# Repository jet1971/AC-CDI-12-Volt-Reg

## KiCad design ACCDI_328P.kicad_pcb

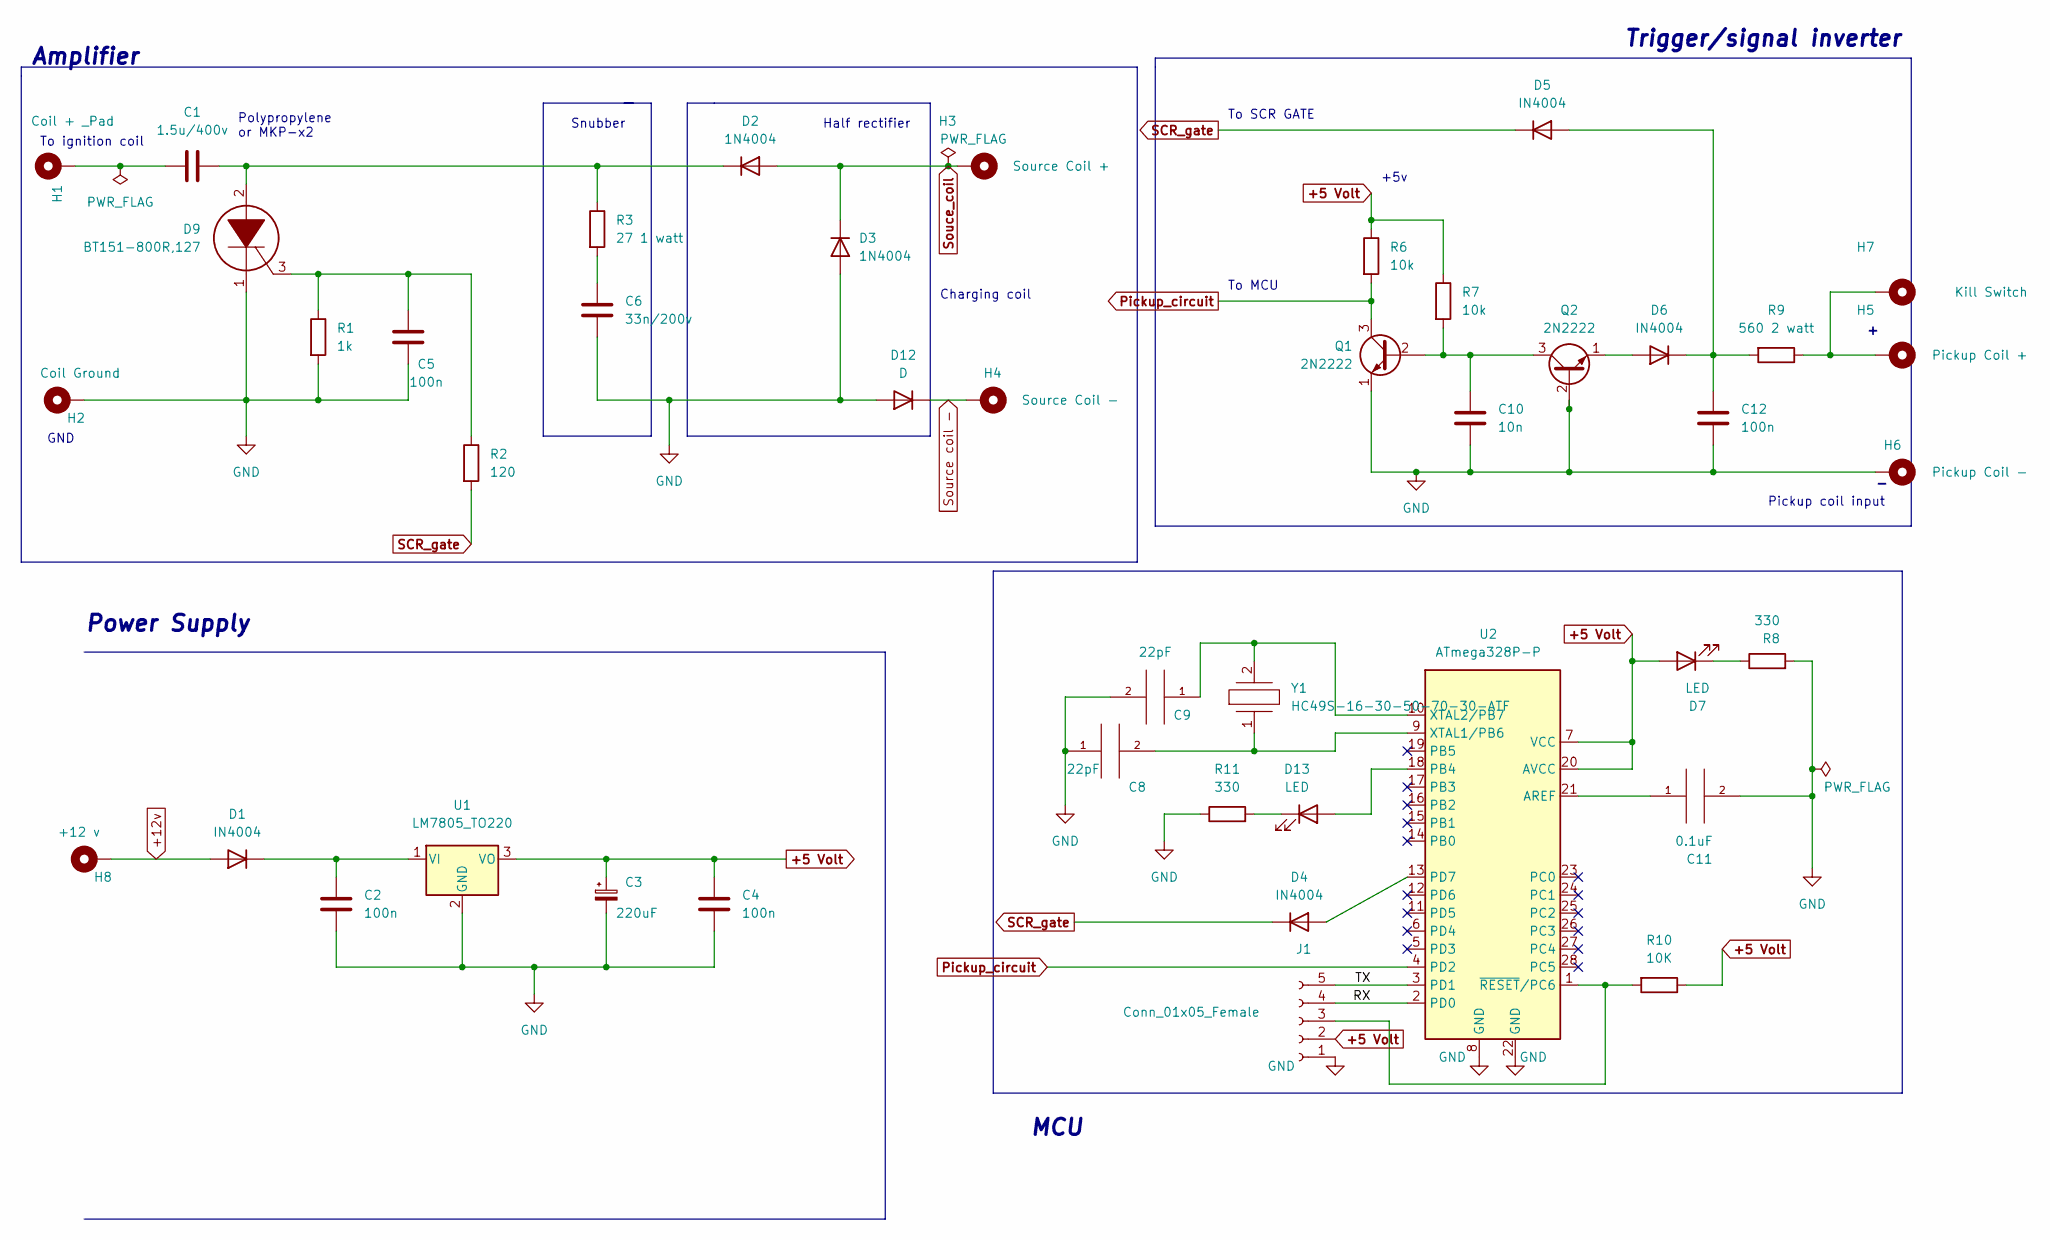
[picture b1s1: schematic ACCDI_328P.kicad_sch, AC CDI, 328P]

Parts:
C1: 1.5u/400v; C_Rect_L26.5mm_W5.0mm_P22.50mm_MKS4
C2, C4, C5, C12: 100n; C_Disc_D6.0mm_W2.5mm_P5.00mm
C3: 220uF; CP_Radial_D10.0mm_P3.50mm
C6: 33n/200v; C_Rect_L9.0mm_W3.2mm_P7.50mm_MKT
C8, C9: 22pF; C_Disc_D5.0mm_W2.5mm_P5.00mm
C10: 10n; C_Disc_D6.0mm_W2.5mm_P5.00mm
C11: 0.1uF; C_Disc_D6.0mm_W2.5mm_P5.00mm
D1, D4, D5, D6: IN4004; D_DO-41_SOD81_P10.16mm_Horizontal
D2, D3: 1N4004; D_DO-41_SOD81_P10.16mm_Horizontal
D7, D13: LED; LED_D3.0mm
D9: BT151-800R,127; TO254P470X1000X2000-3P; Manufacturer_Part_Number BT151-800R,127; Mouser Part Number 771-BT151-800R127
D12: D; D_DO-41_SOD81_P10.16mm_Horizontal
H1: Coil + _Pad; MountingHole_2.2mm_M2_ISO14580_Pad_TopBottom
H2: Coil Ground; MountingHole_2.2mm_M2_Pad_TopBottom
H3: Source Coil +; MountingHole_2.2mm_M2_Pad_TopBottom
H4: Source Coil -; MountingHole_2.2mm_M2_Pad_TopBottom
H5: Pickup Coil +; MountingHole_2.2mm_M2_Pad_TopBottom
H6: Pickup Coil -; MountingHole_2.2mm_M2_Pad_TopBottom
H7: Kill Switch; MountingHole_2.2mm_M2_Pad_TopBottom
H8: +12 v; MountingHole_2.2mm_M2_Pad_TopBottom
J1: Conn_01x05_Female; PinSocket_1x05_P2.54mm_Vertical
Q1, Q2: 2N2222; TO-92_Inline
R1: 1k; R_Axial_DIN0309_L9.0mm_D3.2mm_P12.70mm_Horizontal
R2: 120; R_Axial_DIN0309_L9.0mm_D3.2mm_P12.70mm_Horizontal
R3: 27 1 watt; R_Axial_DIN0516_L15.5mm_D5.0mm_P20.32mm_Horizontal
R6, R7: 10k; R_Axial_DIN0309_L9.0mm_D3.2mm_P12.70mm_Horizontal
R8, R11: 330; R_Axial_DIN0309_L9.0mm_D3.2mm_P12.70mm_Horizontal
R9: 560 2 watt; R_Axial_DIN0516_L15.5mm_D5.0mm_P20.32mm_Horizontal
R10: 10K; R_Axial_DIN0207_L6.3mm_D2.5mm_P10.16mm_Horizontal
U1: LM7805_TO220; TO-220-3_Vertical
U2: ATmega328P-P; DIP-28_W7.62mm
Y1: HC49S-16-30-50-70-30-ATF; Resonator-2Pin_W10.0mm_H5.0mm; Manufacturer_Part_Number HC49S-16-30-50-70-30-ATF

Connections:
+5 Volt: C3.1, C4.1, D7.2 (A), J1.2, R6.1, R7.1, R10.1, U1.3 (VO), U2.7 (VCC), U2.20 (AVCC)
+12v: D1.2 (A), H8.1
/RX: J1.4, U2.2 (PD0)
/TX: J1.5, U2.3 (PD1)
GND: C2.2, C3.2, C4.2, C5.2, C6.2, C8.1, C9.2, C10.2, C11.2, C12.2, D3.2 (A), D9.1, D12.2 (A), H2.1, H6.1, J1.1, Q1.1 (E), Q2.2 (B), R1.2, R8.2, R11.1, U1.2 (GND), U2.8 (GND), U2.22 (GND)
unnamed: C1.1, D2.1 (K), D9.2, R3.1
unnamed: C1.2, H1.1
unnamed: C2.1, D1.1 (K), U1.1 (VI)
unnamed: C5.1, D9.3, R1.1, R2.1
unnamed: C6.1, R3.2
unnamed: C8.2, U2.9 (XTAL1/PB6), Y1.1
unnamed: C9.1, U2.10 (XTAL2/PB7), Y1.2
unnamed: C10.1, Q1.2 (B), Q2.3 (C), R7.2
unnamed: C11.1, U2.21 (AREF)
unnamed: C12.1, D5.2 (A), D6.1 (K), R9.2
unnamed: D4.2 (A), U2.13 (PD7)
unnamed: D6.2 (A), Q2.1 (E)
unnamed: D7.1 (K), R8.1
unnamed: D13.1 (K), R11.2
unnamed: D13.2 (A), U2.18 (PB4)
unnamed: H5.1, H7.1, R9.1
unnamed: J1.3, R10.2, U2.1 (~RESET/PC6)
Pickup_circuit: Q1.3 (C), R6.2, U2.4 (PD2)
SCR_gate: D4.1 (K), D5.1 (K), R2.2
Souce_coil: D2.2 (A), D3.1 (K), H3.1
Source coil -: D12.1 (K), H4.1

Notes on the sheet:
Power Supply
MCU
Snubber
To ignition coil
Trigger/signal inverter
Charging coil
To SCR GATE
Polypropylene or MKP-x2
Half rectifier
+5v
Pickup coil input
Amplifier
GND
To MCU

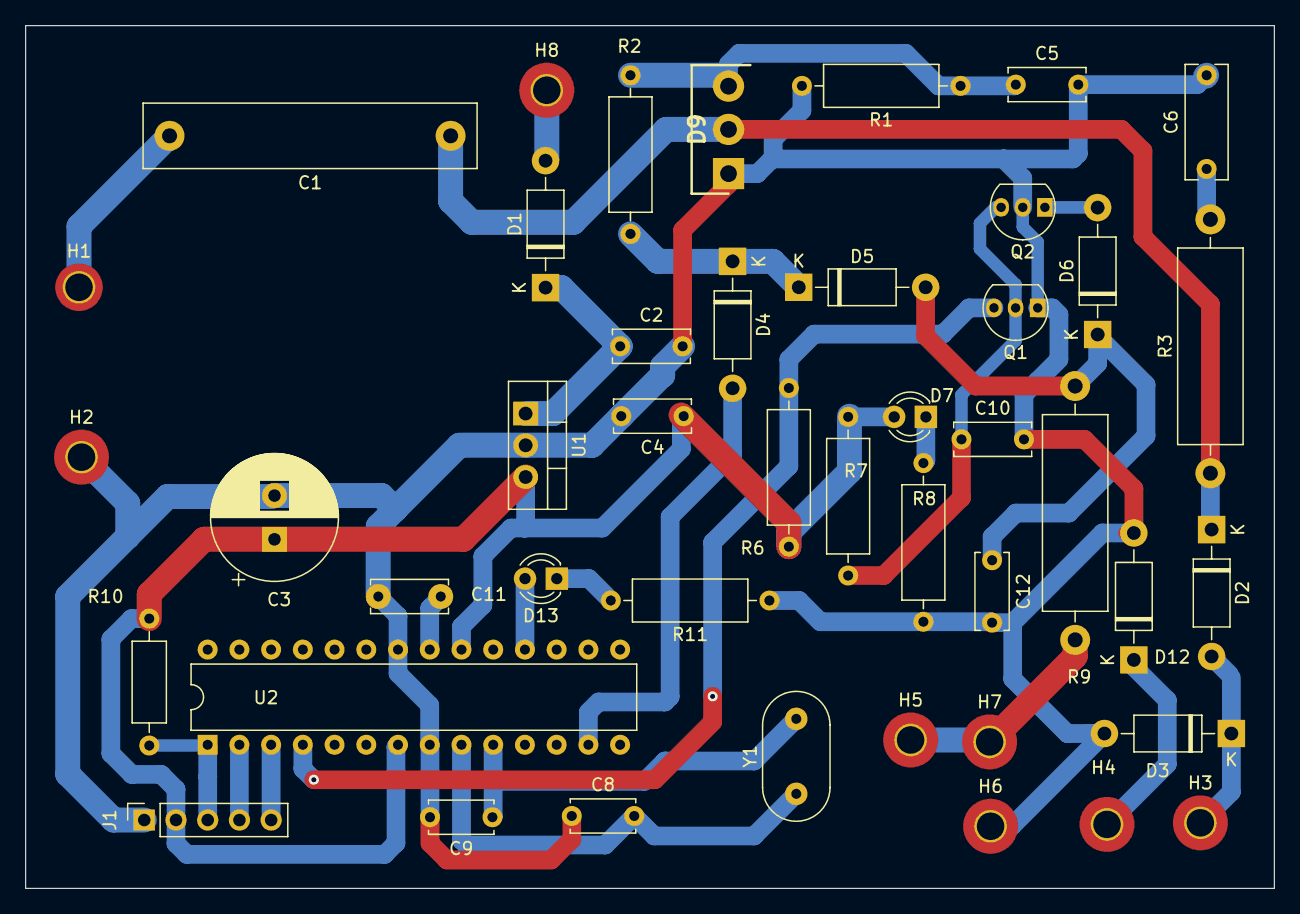
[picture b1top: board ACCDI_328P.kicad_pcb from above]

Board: 2 copper layers, 100.0 x 69.1 mm, 44 parts (0 on the bottom side), 26 nets.

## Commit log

2022-09-14 12volt reg version
